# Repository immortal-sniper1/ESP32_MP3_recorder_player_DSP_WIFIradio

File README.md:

# ESP32_MP3_recorder_player_DSP_WIFIradio

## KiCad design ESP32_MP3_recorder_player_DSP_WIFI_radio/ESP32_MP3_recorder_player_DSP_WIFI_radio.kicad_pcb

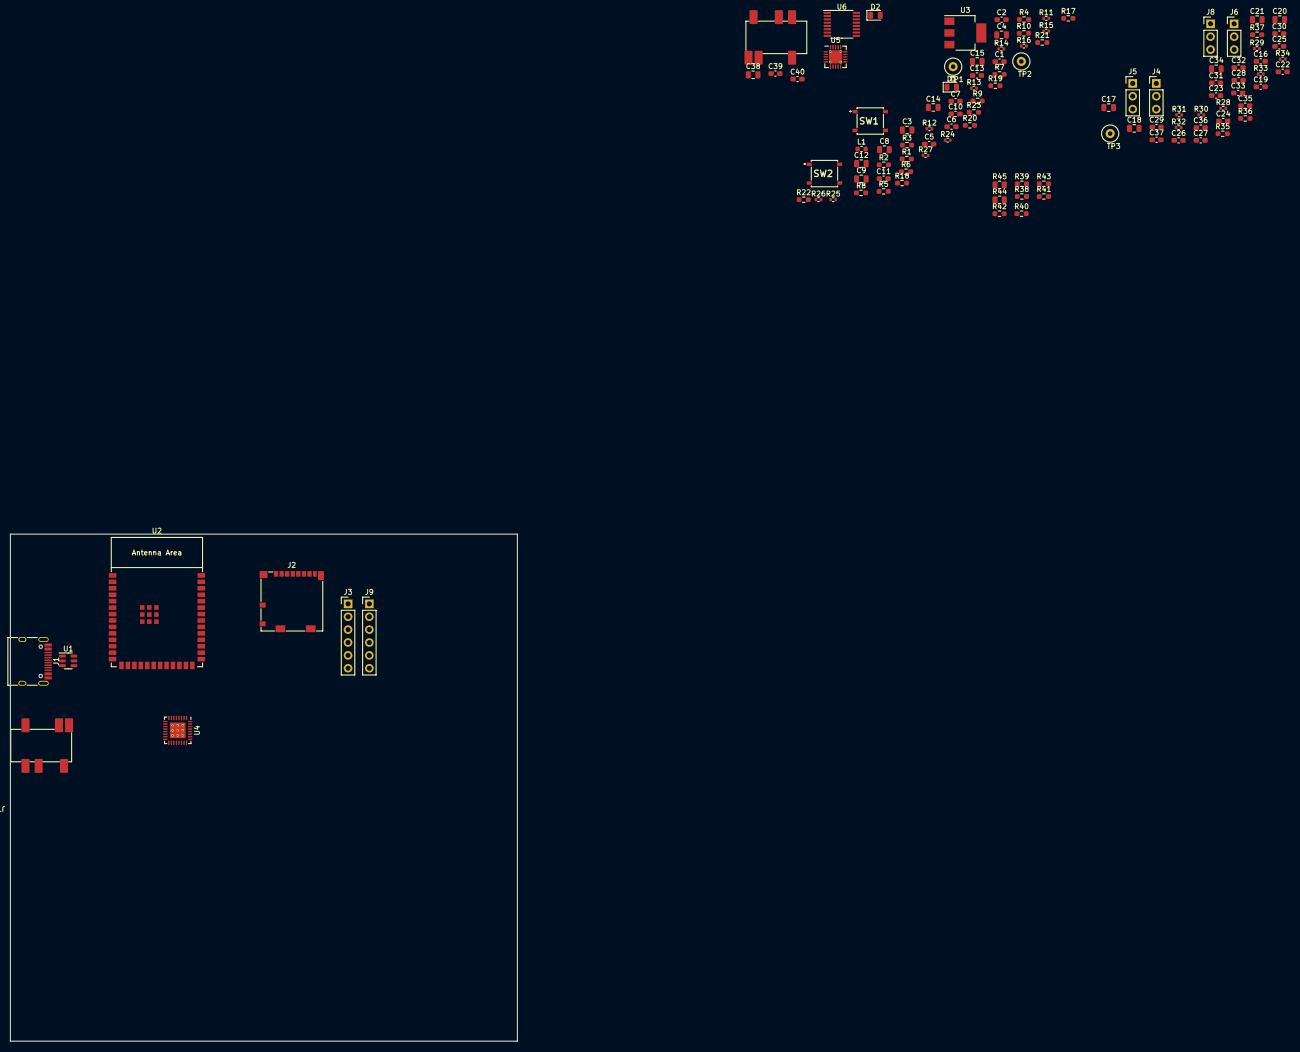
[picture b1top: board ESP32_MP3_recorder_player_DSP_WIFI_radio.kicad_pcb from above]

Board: 2 copper layers, 100.0 x 100.0 mm, 109 parts (0 on the bottom side), 97 nets, no tracks yet.

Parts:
C1, C2, C6, C7, C10, C13, C16, C19, C22, C39, C40: 100n; C_0603_1608Metric_Pad1.08x0.95mm_HandSolder
C3: 470n; C_0805_2012Metric
C4: 2u2; C_0805_2012Metric
C5: DNP; C_0603_1608Metric_Pad1.08x0.95mm_HandSolder
C8, C9, C12, C14, C15, C17, C18, C20, C21, C34, C38: 10u; C_0805_2012Metric
C11: 15p; C_0603_1608Metric_Pad1.08x0.95mm_HandSolder
C23, C24, C25, C26, C27, C28, C29, C31, C32, C35, C36, C37: 1u; C_0603_1608Metric_Pad1.08x0.95mm_HandSolder
C30, C33: 4n7; C_0603_1608Metric_Pad1.08x0.95mm_HandSolder
D1, D2: LED_Small; LED_0805_2012Metric
J1: USB_C_Receptacle; USB_C_Receptacle_HRO_TYPE-C-31-M-12
J2: Micro_SD_Card_Det; microSD_HC_Molex_104031-0811
J3, J9: Conn_01x06; PinHeader_1x06_P2.54mm_Vertical
J4, J5, J6, J8: AUDIO; PinHeader_1x03_P2.54mm_Vertical
J7, J10: AudioJack4_SwitchTR1; PJ-316A-6A
L1: L_Small; L_0603_1608Metric
R1, R36, R37: 2k7; R_0603_1608Metric_Pad0.98x0.95mm_HandSolder
R2, R3, R35, R38, R39, R40, R41, R42, R43: 1k; R_0603_1608Metric_Pad0.98x0.95mm_HandSolder
R4, R5: 300; R_0603_1608Metric_Pad0.98x0.95mm_HandSolder
R6, R9, R17, R18, R19, R20, R21, R22, R23: 10k; R_0603_1608Metric_Pad0.98x0.95mm_HandSolder
R7, R8: 5k1; R_0603_1608Metric_Pad0.98x0.95mm_HandSolder
R10: 1Meg; R_0603_1608Metric_Pad0.98x0.95mm_HandSolder
R11, R12, R13, R14, R15, R16, R24, R25, R27, R28, R29, R31: 10; R_0402_1005Metric
R26, R30, R32, R33, R34: 27; R_0402_1005Metric
R44, R45: 100k; R_0805_2012Metric
SW1, SW2: MCU_RESET; PTS526SK15SMTR2LFS
TP1, TP2, TP3: TestPoint_THT; TestPoint_Loop_D2.60mm_Drill0.9mm_Beaded
U1: SRV05-4; SOT-23-6
U2: ESP32-S3-WROOM-1
U3: AMS1117-3.3; SOT-223-3_TabPin2
U4: TLV320AIC3254; QFN-32-1EP_5x5mm_P0.5mm_EP3.1x3.1mm_ThermalVias
U5: TPA2012D2; QFN-20-1EP_4x4mm_P0.5mm_EP2.6x2.6mm_ThermalVias
U6: PCA9557PW; TSSOP-16_4.4x5mm_P0.65mm

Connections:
+3V3: C8.1, C9.1, C10.1, C12.1, C13.1, C15.1, C20.1, C21.1, C22.1, D1.2 (A), J2.4 (VDD), J3.2, J9.2, R2.1, R3.2, R6.1, R9.2, R17.2, R18.2, R19.2, R20.2, R21.2, R22.2, R23.2, R45.1, U2.2 (3V3), U3.2 (VO), U4.6 (IOVDD), U4.26 (LDOIN/HPVDD), U4.30 (LDO_SELECT)
+5V: C1.1, C2.1, C14.1, C38.1, C39.1, L1.1, R1.1, U3.3 (VI), U5.3 (PVDD), U5.13 (PVDD), U6.16 (VDD)
/Audio_Codec/BCLK: R32.2, U4.2 (BCLK)
/Audio_Codec/DIN: R34.2, U4.4 (DIN/MFP1)
/Audio_Codec/DOUT: R33.2, U4.5 (DOUT/MFP2)
/Audio_Codec/MCLK: R28.2, U4.1 (MCLK)
/Audio_Codec/RESET: R26.2, U4.31 (~RESET)
/Audio_Codec/WCLK: R30.2, U4.3 (WCLK)
/CARD_DETECT: J2.10 (DET_A), R23.1, R24.1
/CLK: J2.5 (CLK), R16.1, R22.1
/CMD: J2.3 (CMD), R15.1, R21.1
/DATA_0: J2.7 (DAT0), R11.1, R17.1
/DATA_1: J2.8 (DAT1), R12.1, R18.1
/DATA_2: J2.1 (DAT2), R13.1, R19.1
/DATA_3: J2.2 (DAT3/CD), R14.1, R20.1
/ESP_BOOT: C7.1, R9.1, SW2.1 (A), U2.27 (GPIO0/BOOT)
/ESP_EN: C5.1, C6.2, R6.2, SW1.1 (A), U2.3 (EN)
/I2S_1_SCK: J3.4, R29.2
/I2S_1_SD: J3.5, R27.2
/I2S_1_WS: J3.6, R25.2
/I2S_1_X: J3.3, R31.2
/cc1: J1.A5 (CC1), R7.1
/cc2: J1.B5 (CC2), R8.1
Audio_OUT_L: C28.1, C30.1, R42.2
Audio_OUT_R: C32.1, C33.1, R43.1
D+: J1.A6 (D+), J1.B6 (D+), U1.4 (IO3), U2.14 (GPIO20/U1CTS/ADC2_CH9/CLK_OUT1/USB_D+)
D-: J1.A7 (D-), J1.B7 (D-), U1.6 (IO4), U2.13 (GPIO19/U1RTS/ADC2_CH8/CLK_OUT2/USB_D-)
GND: C1.2, C2.2, C5.2, C6.1, C7.2, C8.2, C9.2, C10.2, C11.2, C12.2, C13.2, C14.2, C15.2, C16.2, C17.2, C18.2, C19.2, C20.2, C21.2, C22.2, C30.2, C31.1, C33.2, C34.2, C36.1, C38.2, C39.2, C40.2, J1.A1 (GND), J1.A12 (GND), J1.B1 (GND), J1.B12 (GND), J2.6 (VSS), J2.9 (DET_B), J2.11 (SHIELD), J3.1, J4.1, J5.1, J6.1, J7.R2, J8.1, J9.1, J10.T, R5.1, R7.2, R8.2, R10.1, R39.2, R40.2, R41.2, R44.2, SW1.2 (B), SW2.2 (B), U1.2 (VN), U2.1 (GND), U2.40 (GND), U2.41 (GND), U3.1 (GND), U4.7 (IOVSS), U4.17 (AVSS), U4.28 (DVSS), U4.33 (EP), U5.4 (PGND), U5.5 (OUTL-), U5.12 (PGND), U5.17 (OUTR-), U5.18 (AGND), U5.21 (PAD), U6.5 (A2), U6.8 (VSS)
GPIO_1: R13.2, U2.39 (GPIO1/TOUCH1/ADC1_CH0)
GPIO_2: R14.2, U2.38 (GPIO2/TOUCH2/ADC1_CH1)
GPIO_11: R33.1, U2.19 (GPIO11/TOUCH11/ADC2_CH0/FSPID/FSPIIO5/S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)
GPIO_12: R34.1, U2.20 (GPIO12/TOUCH12/ADC2_CH1/FSPICLK/FSPIIO6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)
GPIO_13: J7.TN, R45.2, U2.21 (GPIO13/TOUCH13/ADC2_CH2/FSPIQ/FSPIIO7/S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)
GPIO_14: R30.1, U2.22 (GPIO14/TOUCH14/ADC2_CH3/FSPIWP/FSPIDQS/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)
GPIO_21: R32.1, U2.23 (GPIO21)
GPIO_35: J9.3, U2.28 (SPIIO6/GPIO35/FSPID/SUBSPID)
GPIO_36: R25.1, U2.29 (SPIIO7/GPIO36/FSPICLK/SUBSPICLK)
GPIO_37: R27.1, U2.30 (SPIDQS/GPIO37/FSPIQ/SUBSPIQ)
GPIO_38: R29.1, U2.31 (GPIO38/FSPIWP/SUBSPIWP)
GPIO_39: R31.1, U2.32 (MTCK/GPIO39/CLK_OUT3/SUBSPICS1)
GPIO_40: R24.2, U2.33 (MTDO/GPIO40/CLK_OUT2)
GPIO_41: R12.2, U2.34 (MTDI/GPIO41/CLK_OUT1)
GPIO_42: R11.2, U2.35 (MTMS/GPIO42)
GPIO_43: R15.2, U2.37 (U0TXD/GPIO43/CLK_OUT1)
GPIO_44: R16.2, U2.36 (U0RXD/GPIO44/CLK_OUT2)
GPIO_47: R28.1, U2.24 (GPIO47/SPICLK_P/SUBSPICLK_P_DIFF)
GPIO_48: R26.1, U2.25 (GPIO48/SPICLK_N/SUBSPICLK_N_DIFF)
MFP3: J9.5, U4.8 (SCLK/MFP3)
MFP4: J9.4, U4.11 (MISO/MFP4)
MFP5: J9.6, U4.32 (GPIO/MFP5)
unnamed: C11.1, J1.S1 (SHIELD), R10.2
unnamed: C16.1, C17.1, U4.24 (AVDD)
unnamed: C18.1, C19.1, U4.29 (DVDD)
unnamed: C23.1, J4.3, R35.2
unnamed: C23.2, U4.13 (IN1_L)
unnamed: C24.1, J4.2, R39.1
unnamed: C24.2, U4.14 (IN1_R)
unnamed: C25.1, J5.3, R38.2
unnamed: C25.2, U4.15 (IN2_L)
unnamed: C26.1, J5.2, R40.1
unnamed: C26.2, U4.16 (IN2_R)
unnamed: C27.1, J7.S, R37.2
unnamed: C27.2, U4.21 (IN3_R)
unnamed: C28.2, U5.20 (INL+)
unnamed: C29.1, R36.2, TP3.1
unnamed: C29.2, U4.20 (IN3_L)
unnamed: C31.2, U5.19 (INL-)
unnamed: C32.2, J8.3
unnamed: C34.1, U4.18 (REF)
unnamed: C35.1, J7.R1
unnamed: C35.2, U4.27 (HPR)
unnamed: C36.2, J8.2
unnamed: C37.1, J7.T, R44.1
unnamed: C40.1, L1.2, U5.9 (AVDD)
unnamed: D1.1 (K), R4.2
unnamed: D2.1 (K), R5.2
unnamed: D2.2 (A), U6.14 (IO7)
unnamed: R1.2, U6.15 (~RESET)
unnamed: R2.2, U6.3 (A0)
unnamed: R3.1, U6.4 (A1)
unnamed: R4.1, U6.13 (IO6)
unnamed: R35.1, R36.1, R37.1, R38.1, U4.19 (MICBIAS)
unnamed: R41.1, U4.12 (SPI_SELECT)
unnamed: R42.1, U4.22 (LOL)
unnamed: R43.2, U4.23 (LOR)
unnamed: TP1.1, U6.11 (IO4)
unnamed: TP2.1, U6.12 (IO5)
unnamed: C37.2, U4.25 (HPL)
unnamed: U5.1 (G1), U6.9 (IO2)
unnamed: J6.3, J10.R2, U5.2 (OUTL+)
unnamed: U5.7 (~SDL), U6.7 (IO1)
unnamed: U5.8 (~SDR), U6.6 (IO0)
unnamed: U5.15 (G0), U6.10 (IO3)
unnamed: J6.2, J10.R1, U5.16 (OUTR+)
SCL: U4.9 (SCL/~SS), U6.1 (SCL)
SDA: U4.10 (SDA/MOSI), U6.2 (SDA)
VBUS: J1.A4 (VBUS), J1.A9 (VBUS), J1.B4 (VBUS), J1.B9 (VBUS), U1.5 (VP)

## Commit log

2023-02-26 Update fp-info-cache
